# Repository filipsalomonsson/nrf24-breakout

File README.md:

# NRF24L01 Breakout Board

A simple little 18x19mm breakout board to make the NRF24L01+ RF tranceiver reasonably breadboard-friendly.

Components:

* 2x 1x5 pin header
* 1x 2x4 socket header
* 1x AZ1117-3.3 voltage regulator (SOT-223)
* 2x 0805 SMD 10uF capacitor
* 1x 0805 SMD LED
* 1x 1kohm 0805 SMD resistor

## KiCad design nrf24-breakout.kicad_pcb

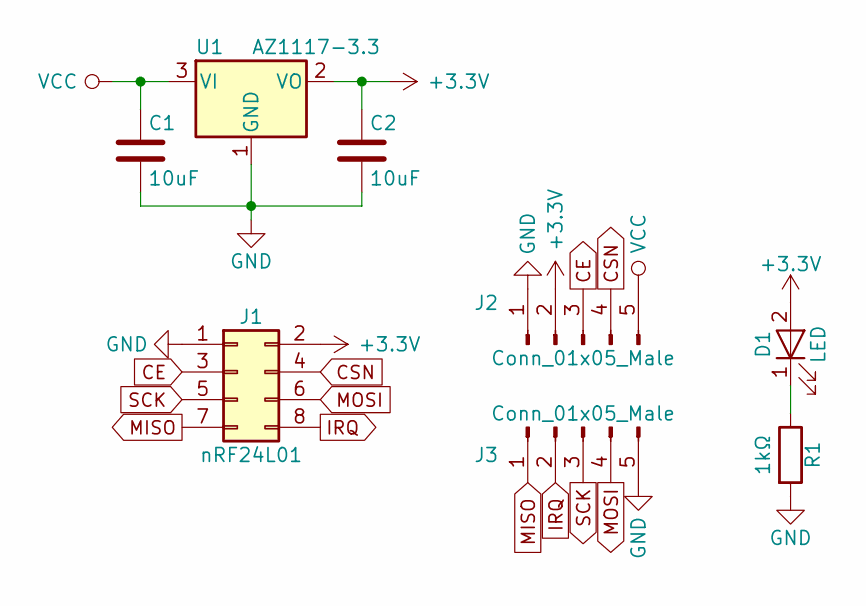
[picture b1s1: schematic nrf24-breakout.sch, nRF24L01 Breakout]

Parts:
C1, C2: 10uF; C_0805_HandSoldering
D1: LED; LED_0805_HandSoldering
J1: nRF24L01; Socket_Strip_Straight_2x04_Pitch2.54mm
J2, J3: Conn_01x05_Male; Pin_Header_Straight_1x05_Pitch2.54mm
R1: 1kΩ; R_0805_HandSoldering
U1: AZ1117-3.3; SOT-223-3Lead_TabPin2

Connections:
+3V3: C2.1, D1.2 (A), J1.2, J2.2, U1.2 (VO)
CE: J1.3, J2.3
CSN: J1.4, J2.4
GND: C1.2, C2.2, J1.1, J2.1, J3.5, R1.2, U1.1 (GND)
IRQ: J1.8, J3.2
MISO: J1.7, J3.1
MOSI: J1.6, J3.4
unnamed: D1.1 (K), R1.1
SCK: J1.5, J3.3
VCC: C1.1, J2.5, U1.3 (VI)

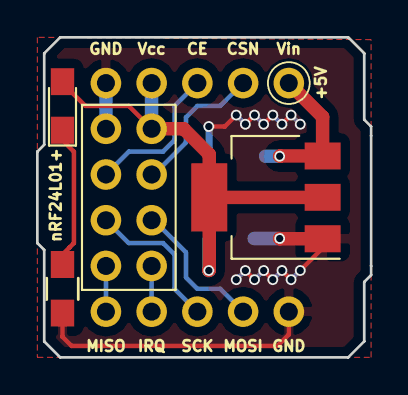
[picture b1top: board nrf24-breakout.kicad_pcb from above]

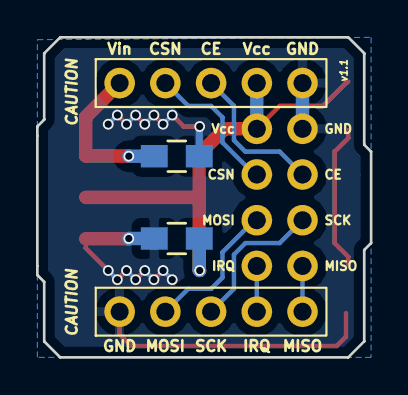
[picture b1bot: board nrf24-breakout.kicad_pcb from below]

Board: 2 copper layers, 18.5 x 17.8 mm, 8 parts (4 on the bottom side), 10 nets.

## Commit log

2018-09-14 Import
2018-09-14 Put gerbers into subfolder
2018-09-14 Add a readme
